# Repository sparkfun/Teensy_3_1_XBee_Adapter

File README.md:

SparkFun Teensy 3.1 XBee Adapter
=================================

[*SparkFun Teensy 3.1 XBee Adapter (BOB-13311)*](https://www.sparkfun.com/products/13311)

Adapter board from the Teensy3.1 to XBee radio modules.

Repository Contents
-------------------

* **/Documentation** - Datasheets, tutorial images. 
* **/Firmware** - Example code 
* **/Hardware** - Eagle design files (.brd, .sch)
* **/Production** - Production panel files (.brd)

Documentation
--------------
* **[Hookup Guide](https://learn.sparkfun.com/tutorials/teensy-xbee-adapter-hookup-guide)** - Basic hookup guide for the Teensy XBee Adapter.

License Information
-------------------
This product is _**open source**_! 

The **hardware** is released under [Creative Commons ShareAlike 4.0 International](https://creativecommons.org/licenses/by-sa/4.0/).
The firmware is released under the [MIT License](http://opensource.org/licenses/MIT). 

Please use, reuse, and modify these files as you see fit. Please maintain attribution to SparkFun Electronics and release anything derivative under the same license.

Distributed as-is; no warranty is given.

- Your friends at SparkFun.

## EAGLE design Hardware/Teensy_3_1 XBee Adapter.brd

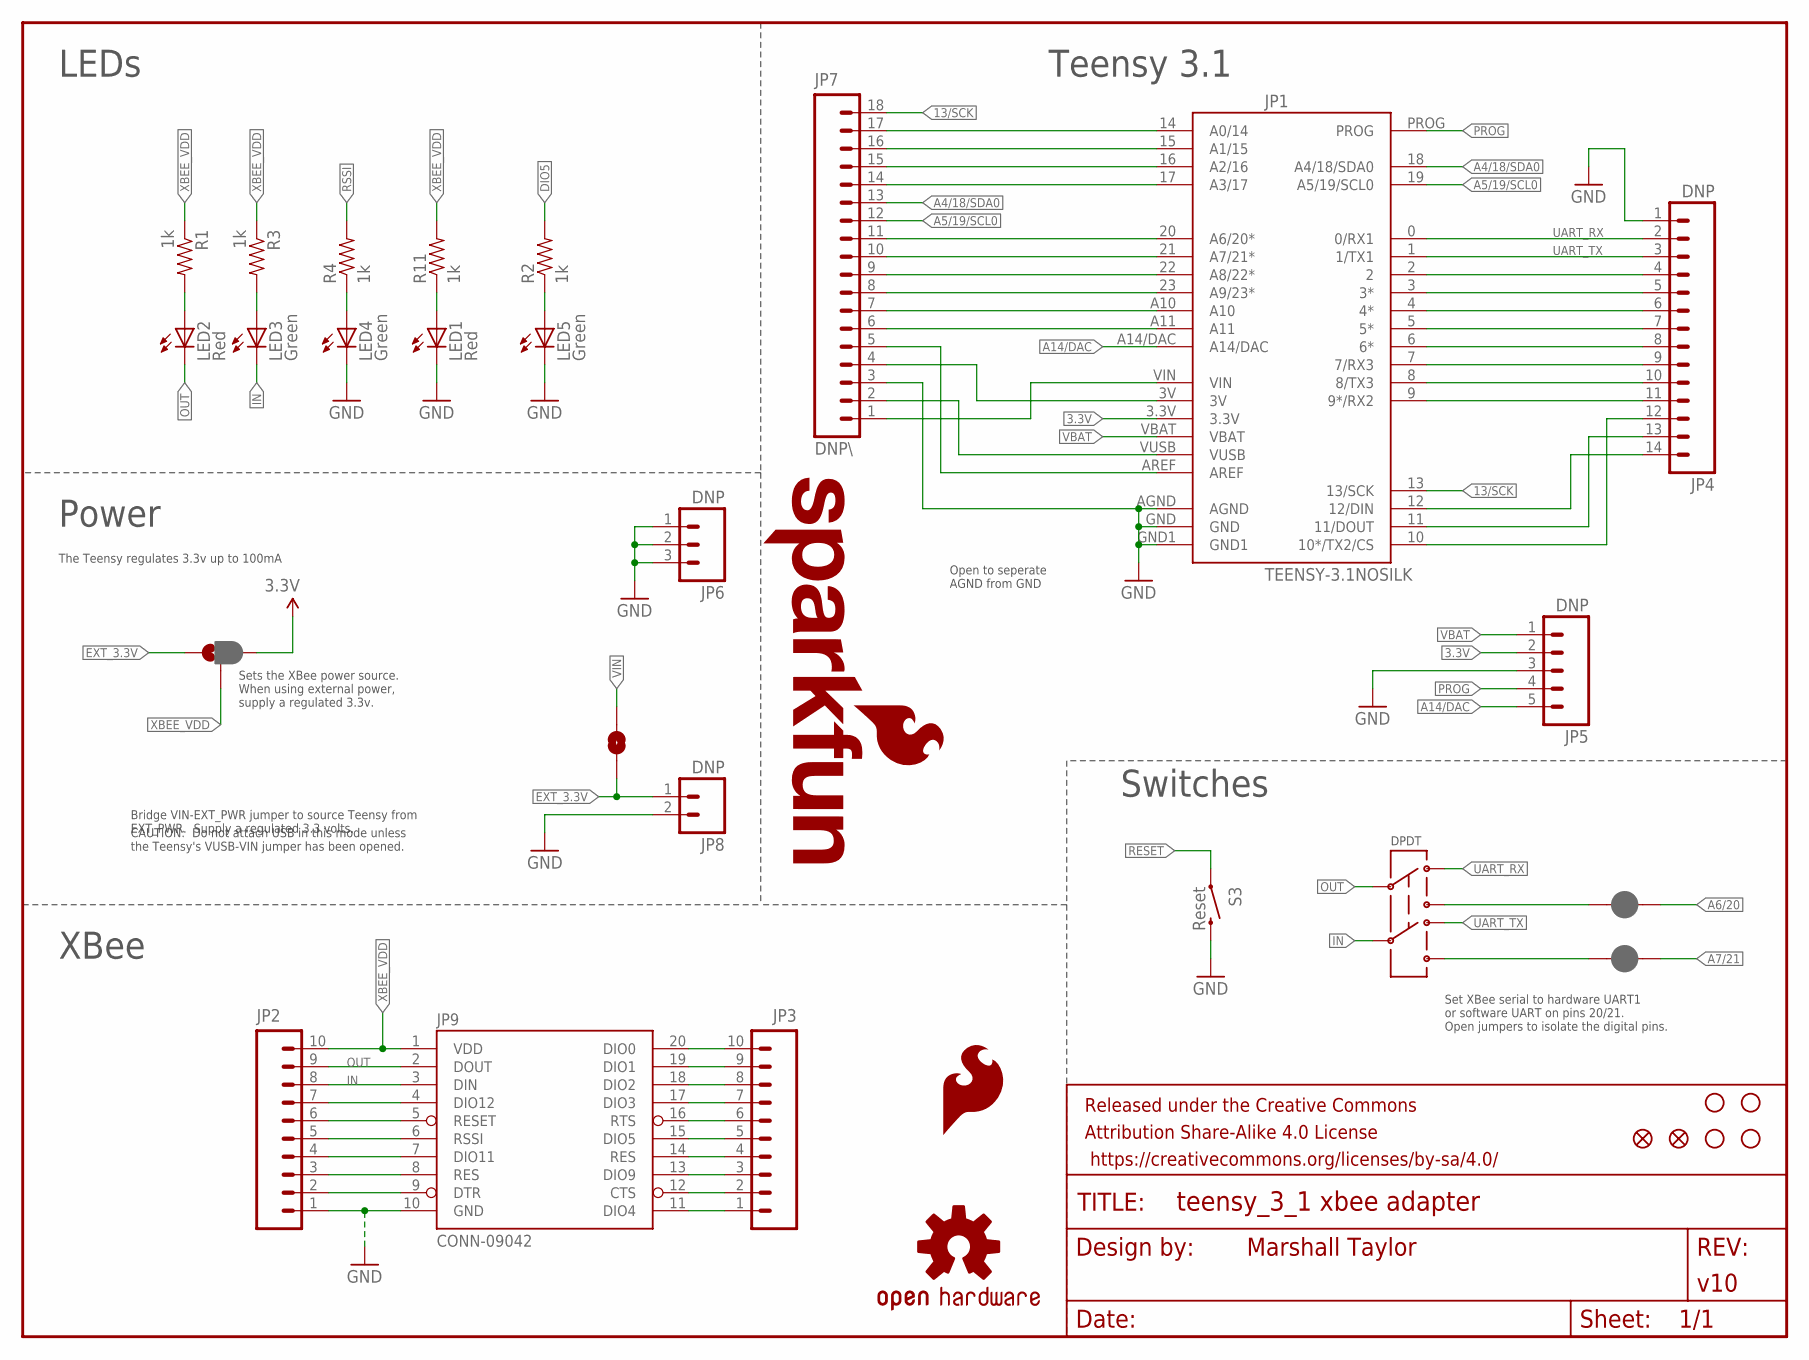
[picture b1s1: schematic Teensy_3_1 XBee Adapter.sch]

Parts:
FID1, FID2: FIDUCIAL1X2; FIDUCIAL-1X2
FRAME1: FRAME-LETTER; CREATIVE_COMMONS
JP1: TEENSY-3.1NOSILK; TEENSY-3.1_NOSILK
JP2, JP3: M10NO_SILK_PTH_FEMALE; 1X10_NO_SILK
JP4: DNP; 1X14
JP5: DNP; 1X05
JP6: DNP; 1X03
JP7: DNP\; 1X18
JP8: DNP; 1X02
JP9: CONN-09042; XBEE-SMD
LED1, LED2: Red; LED-0603
LED3, LED4, LED5: Green; LED-0603
LOGO1: SFE_LOGO_FLAME.2_INCH; SFE_LOGO_FLAME_.2
LOGO2: OSHW-LOGOM; OSHW-LOGO-M
LOGO3: SFE_LOGO_NAME_FLAME.2_INCH; SFE_LOGO_NAME_FLAME_.2
R1, R2, R3, R4, R11: 1k; 0603-RES
S2: DPDT; AYZ0202
S3: Reset; TACTILE-SWITCH-SMD
SJ1: D_TX; PAD-JUMPER-2-NC_BY_PASTE_YES_SILK
SJ3: D_RX; PAD-JUMPER-2-NC_BY_PASTE_YES_SILK
SJ4: JUMPER-PAD-3-2OF3_NC_BY_PASTE; PAD-JUMPER-3-2OF3_NC_BY_PASTE_YES_SILK_FULL_BOX
SJ5: EXT_JPR; PAD-JUMPER-2-NO_YES_SILK
STANDOFF1, STANDOFF2, STANDOFF3, STANDOFF4: STAND-OFF

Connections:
2: JP1.2, JP4.4
3: JP1.3 (3*), JP4.5
3.3V: JP1.3.3V, JP5.2, SJ4.3
3V: JP1.3V, JP7.4
4: JP1.4 (4*), JP4.6
5: JP1.5 (5*), JP4.7
6: JP1.6 (6*), JP4.8
7/RX3: JP1.7 (7/RX3), JP4.9
8/TX3: JP1.8 (8/TX3), JP4.10
9/RX2: JP1.9 (9*/RX2), JP4.11
10/TX2/CS: JP1.10 (10*/TX2/CS), JP4.12
11/DOUT: JP1.11 (11/DOUT), JP4.13
12/DIN: JP1.12 (12/DIN), JP4.14
13/SCK: JP1.13 (13/SCK), JP7.18
A0/14: JP1.14 (A0/14), JP7.17
A1/15: JP1.15 (A1/15), JP7.16
A2/16: JP1.16 (A2/16), JP7.15
A3/17: JP1.17 (A3/17), JP7.14
A4/18/SDA0: JP1.18 (A4/18/SDA0), JP7.13
A5/19/SCL0: JP1.19 (A5/19/SCL0), JP7.12
A6/20: JP1.20 (A6/20*), JP7.11, SJ3.1
A7/21: JP1.21 (A7/21*), JP7.10, SJ1.1
A8/22: JP1.22 (A8/22*), JP7.9
A9/23: JP1.23 (A9/23*), JP7.8
A10: JP1.A10, JP7.7
A11: JP1.A11, JP7.6
A14/DAC: JP1.A14/DAC, JP5.5
AREF: JP1.AREF, JP7.5
CTS: JP3.2, JP9.12 (CTS)
DIO0: JP3.10, JP9.20 (DIO0)
DIO1: JP3.9, JP9.19 (DIO1)
DIO2: JP3.8, JP9.18 (DIO2)
DIO3: JP3.7, JP9.17 (DIO3)
DIO4: JP3.1, JP9.11 (DIO4)
DIO5: JP3.5, JP9.15 (DIO5), R2.2
DIO9: JP3.3, JP9.13 (DIO9)
DIO11: JP2.4, JP9.7 (DIO11)
DIO12: JP2.7, JP9.4 (DIO12)
DTR: JP2.2, JP9.9 (DTR)
EXT_3.3V: JP8.1, SJ4.1, SJ5.2
GND: JP1.AGND, JP1.GND, JP1.GND1, JP2.1, JP4.1, JP5.3, JP6.1, JP6.2, JP6.3, JP7.3, JP8.2, JP9.10 (GND), LED1.C, LED4.C, LED5.C, S3.3 (2)
IN: JP2.8, JP9.3 (DIN), LED3.C, S2.5
unnamed: LED1.A, R11.1
unnamed: LED2.A, R1.2
unnamed: LED3.A, R3.2
unnamed: LED4.A, R4.1
unnamed: LED5.A, R2.1
unnamed: S2.6, SJ1.2
unnamed: S2.3, SJ3.2
OUT: JP2.9, JP9.2 (DOUT), LED2.C, S2.2
PROG: JP1.PROG, JP5.4
RES: JP2.3, JP9.8 (RES)
RES2: JP3.4, JP9.14 (RES)
RESET: JP2.6, JP9.5 (RESET), S3.1
RSSI: JP2.5, JP9.6 (RSSI), R4.2
RTS: JP3.6, JP9.16 (RTS)
UART_RX: JP1.0 (0/RX1), JP4.2, S2.1
UART_TX: JP1.1 (1/TX1), JP4.3, S2.4
VBAT: JP1.VBAT, JP5.1
VIN: JP1.VIN, JP7.1, SJ5.1
VUSB: JP1.VUSB, JP7.2
XBEE_VDD: JP2.10, JP9.1 (VDD), R1.1, R3.1, R11.2, SJ4.2

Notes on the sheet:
Switches
Teensy 3.1
XBee
Power
LEDs
The Teensy regulates 3.3v up to 100mA
Sets the XBee power source. When using external power, supply a regulated 3.3v.
Bridge VIN-EXT_PWR jumper to source Teensy from EXT_PWR. Supply a regulated 3.3 volts.
CAUTION: Do not attach USB in this mode unless the Teensy's VUSB-VIN jumper has been opened.
Set XBee serial to hardware UART1 or software UART on pins 20/21. Open jumpers to isolate the digital pins.
DPDT
Open to seperate AGND from GND

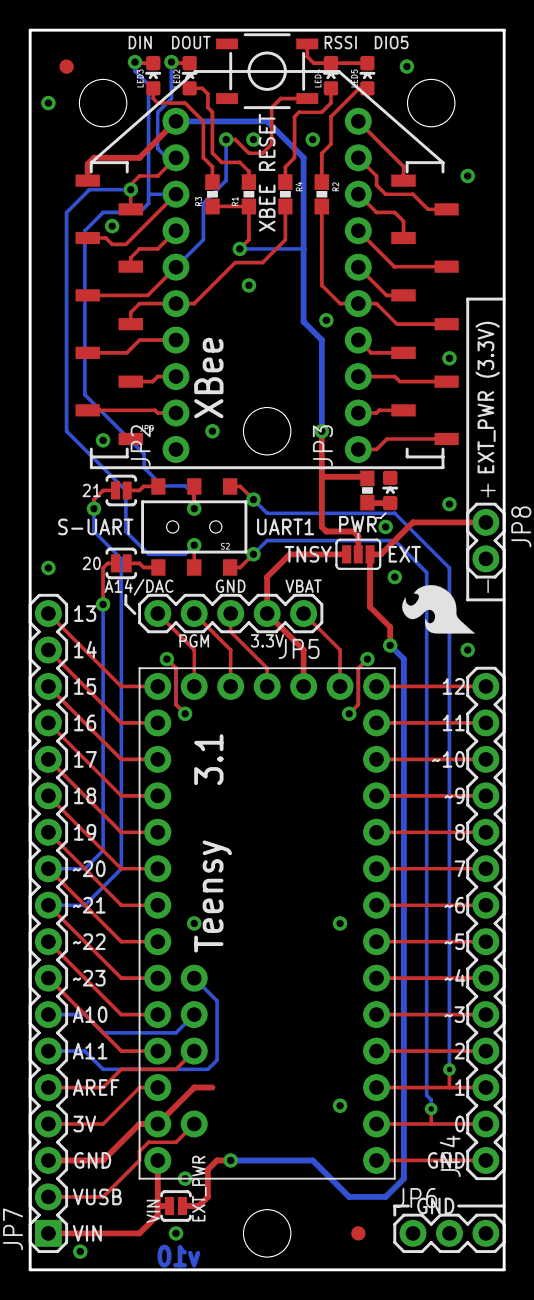
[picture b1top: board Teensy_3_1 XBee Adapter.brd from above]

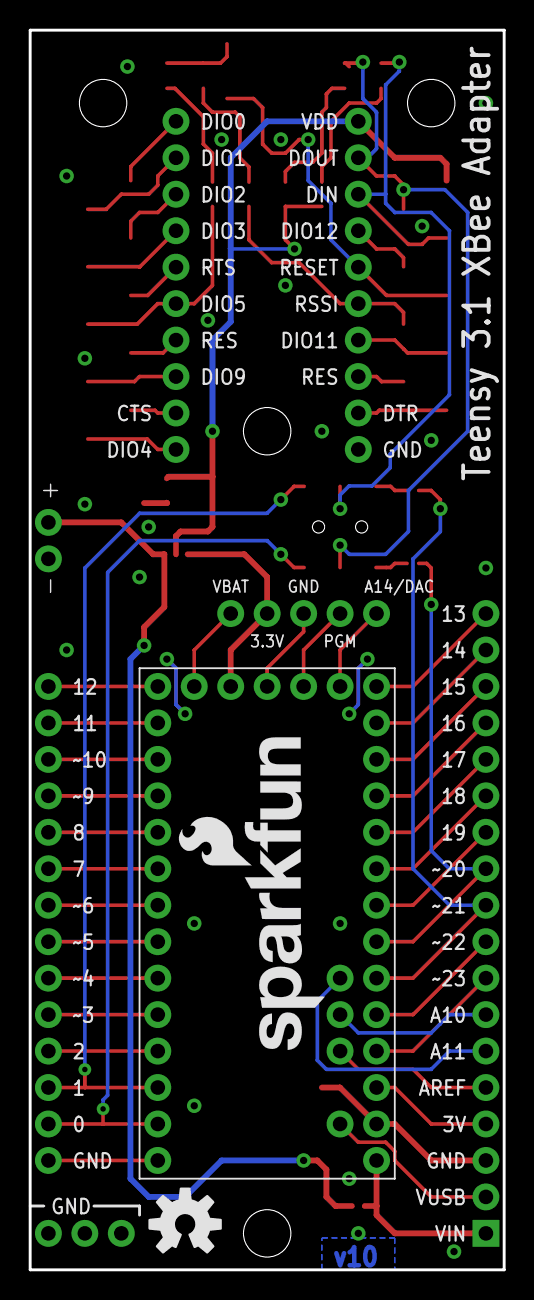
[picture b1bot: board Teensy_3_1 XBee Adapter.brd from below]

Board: 2 copper layers, 33.0 x 86.4 mm, 35 parts (2 on the bottom side), 62 nets.

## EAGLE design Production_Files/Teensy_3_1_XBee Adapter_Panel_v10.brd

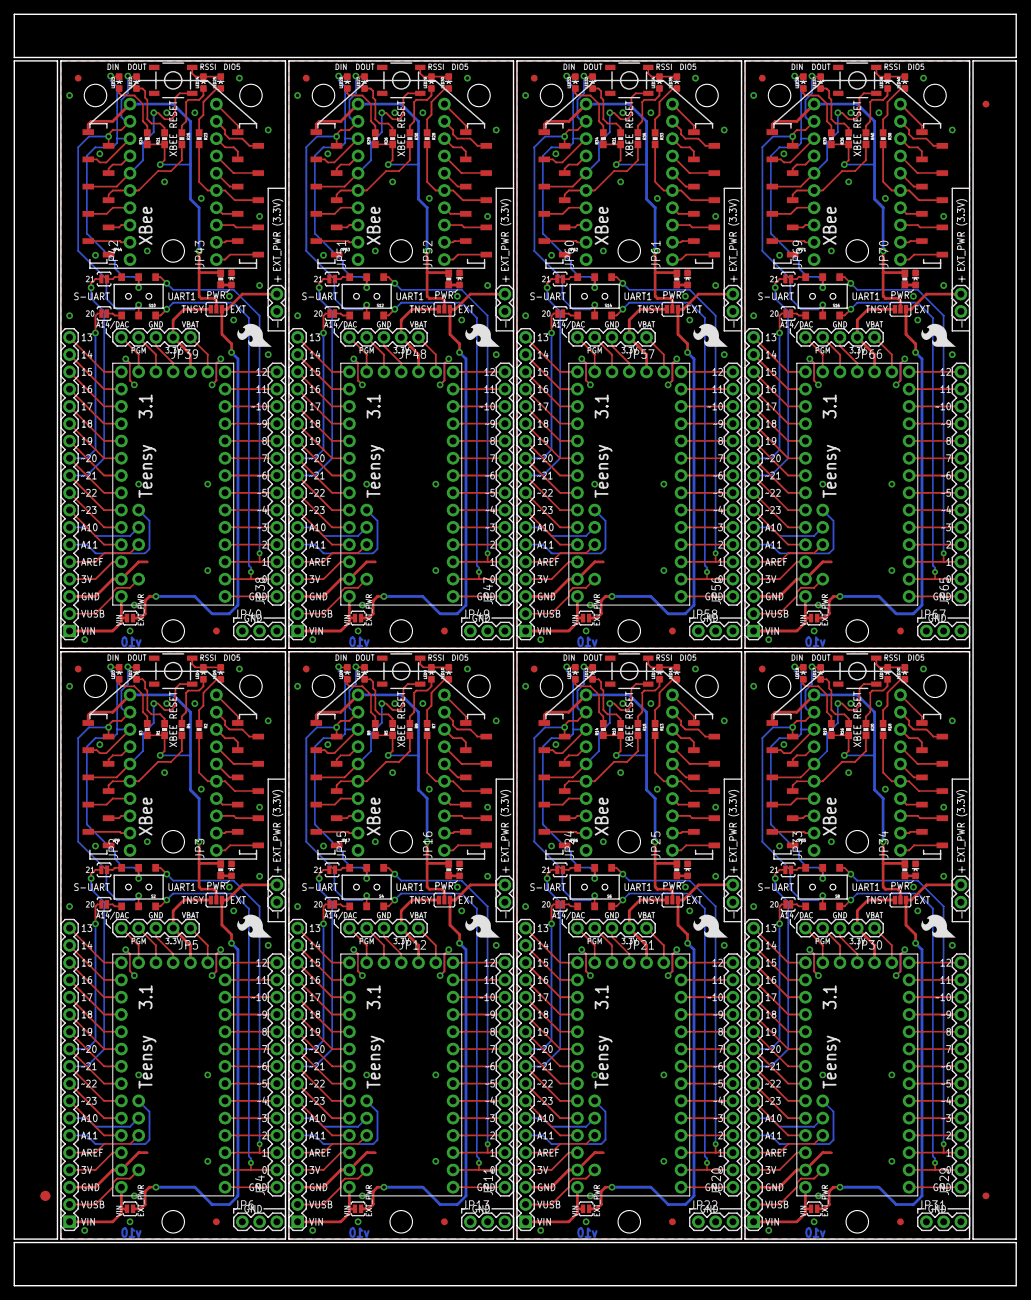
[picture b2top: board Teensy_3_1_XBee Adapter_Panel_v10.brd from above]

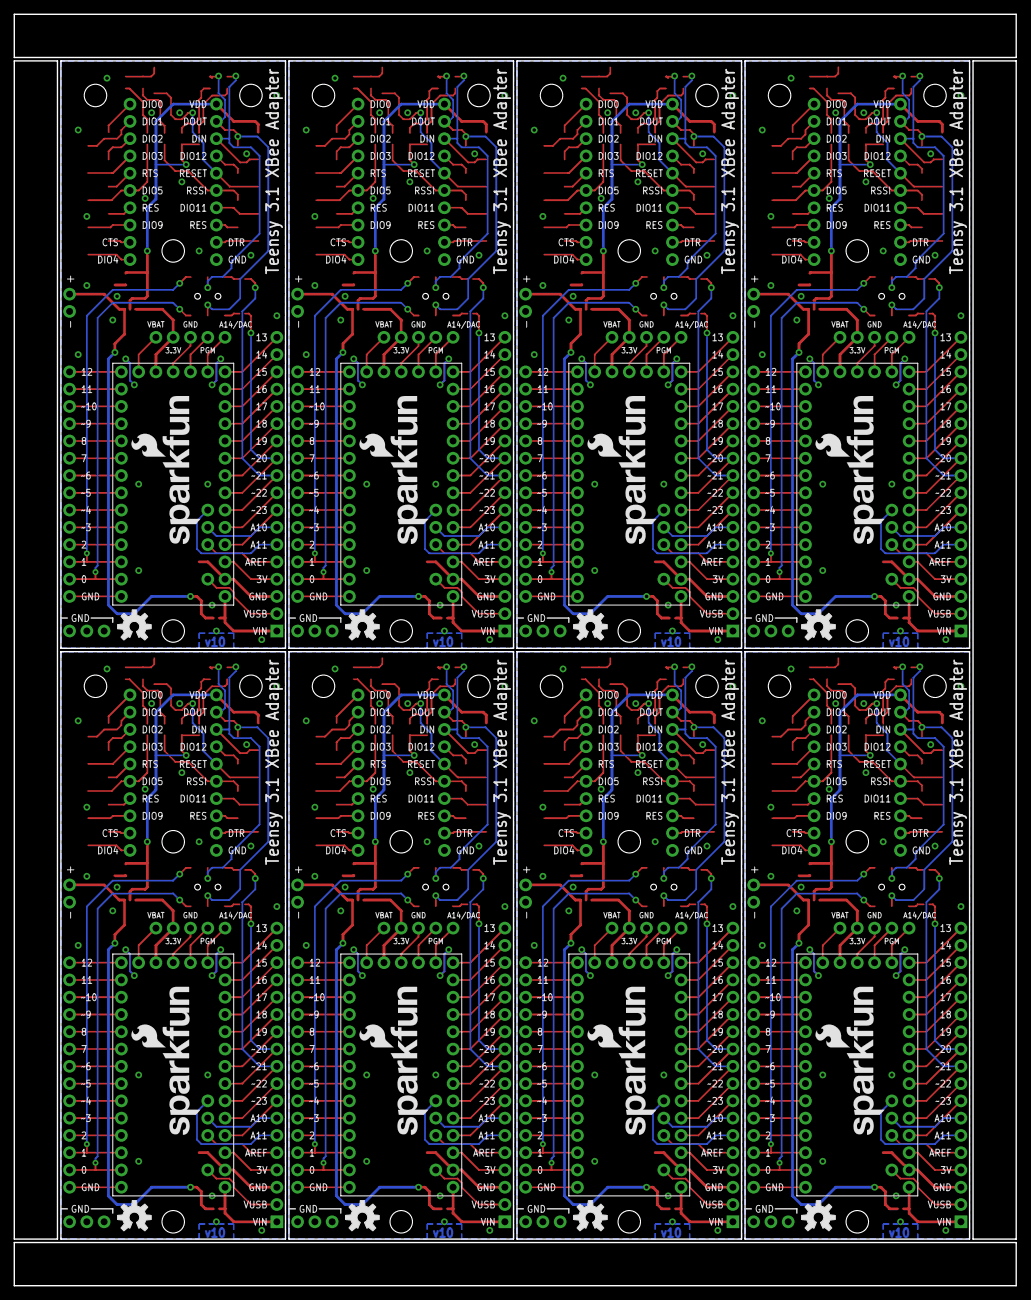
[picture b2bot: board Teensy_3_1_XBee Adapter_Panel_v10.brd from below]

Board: 2 copper layers, 147.3 x 186.9 mm, 275 parts (16 on the bottom side), 496 nets.

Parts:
E$1: FIDUCIAL-1.5X3
E$4, E$5: FIDUCIAL-1X2
FID1, FID2, FID3, FID4, FID5, FID6, FID7, FID8, FID9, FID10, FID11, FID12, FID13, FID14, FID15, FID16: FIDUCIAL1X2; FIDUCIAL-1X2
JP1, JP10, JP19, JP28, JP37, JP46, JP55, JP64: TEENSY-3.1NOSILK; TEENSY-3.1_NOSILK
JP2, JP3, JP15, JP16, JP24, JP25, JP33, JP34, JP42, JP43, JP51, JP52, JP60, JP61, JP69, JP70: 1X10_NO_SILK
JP4, JP11, JP20, JP29, JP38, JP47, JP56, JP65: DNP; 1X14
JP5, JP12, JP21, JP30, JP39, JP48, JP57, JP66: DNP; 1X05
JP6, JP13, JP22, JP31, JP40, JP49, JP58, JP67: DNP; 1X03
JP7, JP14, JP23, JP32, JP41, JP50, JP59, JP68: DNP\; 1X18
JP8, JP18, JP27, JP36, JP45, JP54, JP63, JP72: DNP; 1X02
JP9, JP17, JP26, JP35, JP44, JP53, JP62, JP71: CONN-09042; XBEE-SMD
LED1, LED2, LED6, LED7, LED11, LED12, LED16, LED17, LED21, LED22, LED26, LED27, LED31, LED32, LED36, LED37: Red; LED-0603
LED3, LED4, LED5, LED8, LED9, LED10, LED13, LED14, LED15, LED18, LED19, LED20, LED23, LED24, LED25, LED28, LED29, LED30, LED33, LED34, LED35, LED38, LED39, LED40: Green; LED-0603
LOGO1, LOGO6, LOGO9, LOGO12, LOGO15, LOGO18, LOGO21, LOGO24: SFE_LOGO_FLAME.2_INCH; SFE_LOGO_FLAME_.2
LOGO2, LOGO4, LOGO7, LOGO10, LOGO13, LOGO16, LOGO19, LOGO22: OSHW-LOGOM; OSHW-LOGO-M
LOGO3, LOGO5, LOGO8, LOGO11, LOGO14, LOGO17, LOGO20, LOGO23: SFE_LOGO_NAME_FLAME.2_INCH; SFE_LOGO_NAME_FLAME_.2
R1, R2, R3, R4, R5, R6, R7, R8, R9, R10, R11, R12, R13, R14, R15, R16, R17, R18, R19, R20, R21, R22, R23, R24, R25, R26, R27, R28, R29, R30, R31, R32, R33, R34, R35, R36, R37, R38, R39, R40: 1k; 0603-RES
S1, S3, S5, S7, S9, S11, S13, S15: Reset; TACTILE-SWITCH-SMD
S2, S4, S6, S8, S10, S12, S14, S16: DPDT; AYZ0202
SJ1, SJ2, SJ9, SJ13, SJ17, SJ21, SJ25, SJ29: D_TX; PAD-JUMPER-2-NC_BY_PASTE_YES_SILK
SJ3, SJ6, SJ10, SJ14, SJ18, SJ22, SJ26, SJ30: D_RX; PAD-JUMPER-2-NC_BY_PASTE_YES_SILK
SJ4, SJ7, SJ11, SJ15, SJ19, SJ23, SJ27, SJ31: JUMPER-PAD-3-2OF3_NC_BY_PASTE; PAD-JUMPER-3-2OF3_NC_BY_PASTE_YES_SILK_FULL_BOX
SJ5, SJ8, SJ12, SJ16, SJ20, SJ24, SJ28, SJ32: EXT_JPR; PAD-JUMPER-2-NO_YES_SILK
STANDOFF1, STANDOFF2, STANDOFF3, STANDOFF4, STANDOFF5, STANDOFF6, STANDOFF7, STANDOFF8, STANDOFF9, STANDOFF10, STANDOFF11, STANDOFF12, STANDOFF13, STANDOFF14, STANDOFF15, STANDOFF16, STANDOFF17, STANDOFF18, STANDOFF19, STANDOFF20, STANDOFF21, STANDOFF22, STANDOFF23, STANDOFF24, STANDOFF25, STANDOFF26, STANDOFF27, STANDOFF28, STANDOFF29, STANDOFF30, STANDOFF31, STANDOFF32: STAND-OFF

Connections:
1: JP10.2, JP11.4
2: JP1.2, JP4.4
3: JP1.3, JP4.5
3.3V: JP1.3.3V, JP5.2, SJ4.3
3.3V1: JP10.3.3V, JP12.2, SJ7.3
3.3V2: JP19.3.3V, JP21.2, SJ11.3
3.3V3: JP28.3.3V, JP30.2, SJ15.3
3.3V4: JP37.3.3V, JP39.2, SJ19.3
3.3V5: JP46.3.3V, JP48.2, SJ23.3
3.3V6: JP55.3.3V, JP57.2, SJ27.3
3.3V7: JP64.3.3V, JP66.2, SJ31.3
3V: JP1.3V, JP7.4
3V1: JP10.3V, JP14.4
3V2: JP19.3V, JP23.4
3V3: JP28.3V, JP32.4
3V4: JP37.3V, JP41.4
3V5: JP46.3V, JP50.4
3V6: JP55.3V, JP59.4
3V7: JP64.3V, JP68.4
4: JP1.4, JP4.6
5: JP1.5, JP4.7
6: JP1.6, JP4.8
7: JP10.4, JP11.6
7/RX1: JP10.7, JP11.9
7/RX2: JP19.7, JP20.9
7/RX3: JP1.7, JP4.9
7/RX4: JP28.7, JP29.9
7/RX5: JP37.7, JP38.9
7/RX6: JP46.7, JP47.9
7/RX7: JP55.7, JP56.9
7/RX8: JP64.7, JP65.9
8: JP10.5, JP11.7
8/TX1: JP10.8, JP11.10
8/TX2: JP19.8, JP20.10
8/TX3: JP1.8, JP4.10
8/TX4: JP28.8, JP29.10
8/TX5: JP37.8, JP38.10
8/TX6: JP46.8, JP47.10
8/TX7: JP55.8, JP56.10
8/TX8: JP64.8, JP65.10
9: JP10.6, JP11.8
9/RX1: JP10.9, JP11.11
9/RX2: JP1.9, JP4.11
9/RX3: JP19.9, JP20.11
9/RX4: JP28.9, JP29.11
9/RX5: JP37.9, JP38.11
9/RX6: JP46.9, JP47.11
9/RX7: JP55.9, JP56.11
9/RX8: JP64.9, JP65.11
10: JP10.3, JP11.5
10/TX2/CS: JP1.10, JP4.12
10/TX2/CS1: JP10.10, JP11.12
10/TX2/CS2: JP19.10, JP20.12
10/TX2/CS3: JP28.10, JP29.12
10/TX2/CS4: JP37.10, JP38.12
10/TX2/CS5: JP46.10, JP47.12
10/TX2/CS6: JP55.10, JP56.12
10/TX2/CS7: JP64.10, JP65.12
11: JP19.2, JP20.4
11/DOUT: JP1.11, JP4.13
11/DOUT1: JP10.11, JP11.13
11/DOUT2: JP19.11, JP20.13
11/DOUT3: JP28.11, JP29.13
11/DOUT4: JP37.11, JP38.13
11/DOUT5: JP46.11, JP47.13
11/DOUT6: JP55.11, JP56.13
11/DOUT7: JP64.11, JP65.13
12: JP19.4, JP20.6
12/DIN: JP1.12, JP4.14
12/DIN1: JP10.12, JP11.14
12/DIN2: JP19.12, JP20.14
12/DIN3: JP28.12, JP29.14
12/DIN4: JP37.12, JP38.14
12/DIN5: JP46.12, JP47.14
12/DIN6: JP55.12, JP56.14
12/DIN7: JP64.12, JP65.14
13: JP19.5, JP20.7
13/SCK: JP1.13, JP7.18
13/SCK1: JP10.13, JP14.18
13/SCK2: JP19.13, JP23.18
13/SCK3: JP28.13, JP32.18
13/SCK4: JP37.13, JP41.18
13/SCK5: JP46.13, JP50.18
13/SCK6: JP55.13, JP59.18
13/SCK7: JP64.13, JP68.18
14: JP19.6, JP20.8
15: JP19.3, JP20.5
16: JP28.2, JP29.4
17: JP28.4, JP29.6
18: JP28.5, JP29.7
19: JP28.6, JP29.8
20: JP28.3, JP29.5
21: JP37.2, JP38.4
22: JP37.4, JP38.6
23: JP37.5, JP38.7
24: JP37.6, JP38.8
25: JP37.3, JP38.5
26: JP46.2, JP47.4
27: JP46.4, JP47.6
28: JP46.5, JP47.7
29: JP46.6, JP47.8
30: JP46.3, JP47.5
31: JP55.2, JP56.4
32: JP55.4, JP56.6
33: JP55.5, JP56.7
34: JP55.6, JP56.8
35: JP55.3, JP56.5
36: JP64.2, JP65.4
37: JP64.4, JP65.6
38: JP64.5, JP65.7
39: JP64.6, JP65.8
40: JP64.3, JP65.5
A0/1: JP10.14, JP14.17
A0/2: JP19.14, JP23.17
A0/3: JP28.14, JP32.17
A0/4: JP37.14, JP41.17
A0/5: JP46.14, JP50.17
A0/6: JP55.14, JP59.17
A0/7: JP64.14, JP68.17
A0/14: JP1.14, JP7.17
A1: JP10.A10, JP14.7
A1/1: JP10.15, JP14.16
A1/2: JP19.15, JP23.16
A1/3: JP28.15, JP32.16
A1/4: JP37.15, JP41.16
A1/5: JP46.15, JP50.16
A1/6: JP55.15, JP59.16
A1/7: JP64.15, JP68.16
A1/15: JP1.15, JP7.16
A2: JP10.A11, JP14.6
A2/1: JP10.16, JP14.15
A2/2: JP19.16, JP23.15
A2/3: JP28.16, JP32.15
A2/4: JP37.16, JP41.15
A2/5: JP46.16, JP50.15
A2/6: JP55.16, JP59.15
A2/7: JP64.16, JP68.15
A2/16: JP1.16, JP7.15
A3: JP19.A10, JP23.7
A3/1: JP10.17, JP14.14
A3/2: JP19.17, JP23.14
A3/3: JP28.17, JP32.14
A3/4: JP37.17, JP41.14
A3/5: JP46.17, JP50.14
A3/6: JP55.17, JP59.14
A3/7: JP64.17, JP68.14
A3/17: JP1.17, JP7.14
A4: JP19.A11, JP23.6
A4/18/SDA0: JP1.18, JP7.13
A4/18/SDA1: JP10.18, JP14.13
A4/18/SDA2: JP19.18, JP23.13
A4/18/SDA3: JP28.18, JP32.13
A4/18/SDA4: JP37.18, JP41.13
A4/18/SDA5: JP46.18, JP50.13
A4/18/SDA6: JP55.18, JP59.13
A4/18/SDA7: JP64.18, JP68.13
A5: JP28.A10, JP32.7
A5/19/SCL0: JP1.19, JP7.12
A5/19/SCL1: JP10.19, JP14.12
A5/19/SCL2: JP19.19, JP23.12
A5/19/SCL3: JP28.19, JP32.12
A5/19/SCL4: JP37.19, JP41.12
A5/19/SCL5: JP46.19, JP50.12
A5/19/SCL6: JP55.19, JP59.12
A5/19/SCL7: JP64.19, JP68.12
A6: JP28.A11, JP32.6
A6/1: JP10.20, JP14.11, SJ6.1
A6/2: JP19.20, JP23.11, SJ10.1
A6/3: JP28.20, JP32.11, SJ14.1
A6/4: JP37.20, JP41.11, SJ18.1
A6/5: JP46.20, JP50.11, SJ22.1
A6/6: JP55.20, JP59.11, SJ26.1
A6/7: JP64.20, JP68.11, SJ30.1
A6/20: JP1.20, JP7.11, SJ3.1
A7: JP37.A10, JP41.7
A7/1: JP10.21, JP14.10, SJ2.1
A7/2: JP19.21, JP23.10, SJ9.1
A7/3: JP28.21, JP32.10, SJ13.1
A7/4: JP37.21, JP41.10, SJ17.1
A7/5: JP46.21, JP50.10, SJ21.1
A7/6: JP55.21, JP59.10, SJ25.1
A7/7: JP64.21, JP68.10, SJ29.1
A7/21: JP1.21, JP7.10, SJ1.1
A8: JP37.A11, JP41.6
A8/1: JP10.22, JP14.9
A8/2: JP19.22, JP23.9
A8/3: JP28.22, JP32.9
A8/4: JP37.22, JP41.9
A8/5: JP46.22, JP50.9
A8/6: JP55.22, JP59.9
A8/7: JP64.22, JP68.9
A8/22: JP1.22, JP7.9
A9: JP46.A10, JP50.7
A9/1: JP10.23, JP14.8
A9/2: JP19.23, JP23.8
A9/3: JP28.23, JP32.8
A9/4: JP37.23, JP41.8
A9/5: JP46.23, JP50.8
A9/6: JP55.23, JP59.8
A9/7: JP64.23, JP68.8
A9/23: JP1.23, JP7.8
A10: JP1.A10, JP7.7
A11: JP1.A11, JP7.6
A12: JP46.A11, JP50.6
A13: JP55.A10, JP59.7
A14: JP55.A11, JP59.6
A14/DAC: JP1.A14/DAC, JP5.5
A14/DAC1: JP10.A14/DAC, JP12.5
A14/DAC2: JP19.A14/DAC, JP21.5
A14/DAC3: JP28.A14/DAC, JP30.5
A14/DAC4: JP37.A14/DAC, JP39.5
A14/DAC5: JP46.A14/DAC, JP48.5
A14/DAC6: JP55.A14/DAC, JP57.5
A14/DAC7: JP64.A14/DAC, JP66.5
A15: JP64.A10, JP68.7
A16: JP64.A11, JP68.6
AREF: JP1.AREF, JP7.5
AREF1: JP10.AREF, JP14.5
AREF2: JP19.AREF, JP23.5
AREF3: JP28.AREF, JP32.5
AREF4: JP37.AREF, JP41.5
AREF5: JP46.AREF, JP50.5
AREF6: JP55.AREF, JP59.5
AREF7: JP64.AREF, JP68.5
CTS: JP3.2, JP9.12
CTS1: JP16.2, JP17.12
CTS2: JP25.2, JP26.12
CTS3: JP34.2, JP35.12
CTS4: JP43.2, JP44.12
CTS5: JP52.2, JP53.12
CTS6: JP61.2, JP62.12
CTS7: JP70.2, JP71.12
DIO0: JP3.10, JP9.20
DIO1: JP3.9, JP9.19
DIO2: JP3.8, JP9.18
DIO3: JP3.7, JP9.17
DIO4: JP3.1, JP9.11
DIO5: JP3.5, JP9.15, R2.2
DIO6: JP16.1, JP17.11
DIO7: JP16.3, JP17.13
DIO8: JP16.7, JP17.17
DIO9: JP3.3, JP9.13
DIO10: JP16.8, JP17.18
DIO11: JP2.4, JP9.7
DIO12: JP2.7, JP9.4
DIO13: JP16.9, JP17.19
DIO14: JP16.10, JP17.20
DIO15: JP15.4, JP17.7
DIO16: JP15.7, JP17.4
DIO17: JP16.5, JP17.15, R7.2
DIO18: JP25.1, JP26.11
DIO19: JP25.3, JP26.13
DIO20: JP25.7, JP26.17
DIO21: JP25.8, JP26.18
DIO22: JP25.9, JP26.19
DIO23: JP25.10, JP26.20
DIO24: JP24.4, JP26.7
DIO25: JP24.7, JP26.4
DIO26: JP25.5, JP26.15, R13.2
DIO27: JP34.1, JP35.11
DIO28: JP34.3, JP35.13
DIO29: JP34.7, JP35.17
DIO30: JP34.8, JP35.18
DIO31: JP34.9, JP35.19
DIO32: JP34.10, JP35.20
DIO33: JP33.4, JP35.7
DIO34: JP33.7, JP35.4
DIO35: JP34.5, JP35.15, R18.2
DIO36: JP43.1, JP44.11
DIO37: JP43.3, JP44.13
DIO38: JP43.7, JP44.17
DIO39: JP43.8, JP44.18
DIO40: JP43.9, JP44.19
DIO41: JP43.10, JP44.20
DIO42: JP42.4, JP44.7
DIO43: JP42.7, JP44.4
DIO44: JP43.5, JP44.15, R23.2
DIO45: JP52.1, JP53.11
DIO46: JP52.3, JP53.13
DIO47: JP52.7, JP53.17
DIO48: JP52.8, JP53.18
DIO49: JP52.9, JP53.19
DIO50: JP52.10, JP53.20
DIO51: JP51.4, JP53.7
DIO52: JP51.7, JP53.4
DIO53: JP52.5, JP53.15, R28.2
DIO54: JP61.1, JP62.11
DIO55: JP61.3, JP62.13
DIO56: JP61.7, JP62.17
DIO57: JP61.8, JP62.18
DIO58: JP61.9, JP62.19
DIO59: JP61.10, JP62.20
DIO60: JP60.4, JP62.7
DIO61: JP60.7, JP62.4
DIO62: JP61.5, JP62.15, R33.2
DIO63: JP70.1, JP71.11
DIO64: JP70.3, JP71.13
DIO65: JP70.7, JP71.17
DIO66: JP70.8, JP71.18
DIO67: JP70.9, JP71.19
DIO68: JP70.10, JP71.20
DIO69: JP69.4, JP71.7
DIO70: JP69.7, JP71.4
DIO71: JP70.5, JP71.15, R38.2
DTR: JP2.2, JP9.9
DTR1: JP15.2, JP17.9
DTR2: JP24.2, JP26.9
DTR3: JP33.2, JP35.9
DTR4: JP42.2, JP44.9
DTR5: JP51.2, JP53.9
DTR6: JP60.2, JP62.9
DTR7: JP69.2, JP71.9
EXT_3.3V: JP8.1, SJ4.1, SJ5.2
EXT_3.3V1: JP18.1, SJ7.1, SJ8.2
EXT_3.3V2: JP27.1, SJ11.1, SJ12.2
EXT_3.3V3: JP36.1, SJ15.1, SJ16.2
EXT_3.3V4: JP45.1, SJ19.1, SJ20.2
EXT_3.3V5: JP54.1, SJ23.1, SJ24.2
EXT_3.3V6: JP63.1, SJ27.1, SJ28.2
EXT_3.3V7: JP72.1, SJ31.1, SJ32.2
GND: JP1.AGND, JP1.GND, JP1.GND1, JP2.1, JP4.1, JP5.3, JP6.1, JP6.2, JP6.3, JP7.3, JP8.2, JP9.10, LED1.C, LED4.C, LED5.C, S3.3
GND1: JP10.AGND, JP10.GND, JP10.GND1, JP11.1, JP12.3, JP13.1, JP13.2, JP13.3, JP14.3, JP15.1, JP17.10, JP18.2, LED6.C, LED9.C, LED10.C, S1.3
GND2: JP19.AGND, JP19.GND, JP19.GND1, JP20.1, JP21.3, JP22.1, JP22.2, JP22.3, JP23.3, JP24.1, JP26.10, JP27.2, LED11.C, LED14.C, LED15.C, S5.3
GND3: JP28.AGND, JP28.GND, JP28.GND1, JP29.1, JP30.3, JP31.1, JP31.2, JP31.3, JP32.3, JP33.1, JP35.10, JP36.2, LED16.C, LED19.C, LED20.C, S7.3
GND4: JP37.AGND, JP37.GND, JP37.GND1, JP38.1, JP39.3, JP40.1, JP40.2, JP40.3, JP41.3, JP42.1, JP44.10, JP45.2, LED21.C, LED24.C, LED25.C, S9.3
GND5: JP46.AGND, JP46.GND, JP46.GND1, JP47.1, JP48.3, JP49.1, JP49.2, JP49.3, JP50.3, JP51.1, JP53.10, JP54.2, LED26.C, LED29.C, LED30.C, S11.3
GND6: JP55.AGND, JP55.GND, JP55.GND1, JP56.1, JP57.3, JP58.1, JP58.2, JP58.3, JP59.3, JP60.1, JP62.10, JP63.2, LED31.C, LED34.C, LED35.C, S13.3
GND7: JP64.AGND, JP64.GND, JP64.GND1, JP65.1, JP66.3, JP67.1, JP67.2, JP67.3, JP68.3, JP69.1, JP71.10, JP72.2, LED36.C, LED39.C, LED40.C, S15.3
IN: JP2.8, JP9.3, LED3.C, S2.5
IN1: JP15.8, JP17.3, LED8.C, S4.5
IN2: JP24.8, JP26.3, LED13.C, S6.5
IN3: JP33.8, JP35.3, LED18.C, S8.5
IN4: JP42.8, JP44.3, LED23.C, S10.5
IN5: JP51.8, JP53.3, LED28.C, S12.5
IN6: JP60.8, JP62.3, LED33.C, S14.5
IN7: JP69.8, JP71.3, LED38.C, S16.5
unnamed: S4.6, SJ2.2
unnamed: S4.3, SJ6.2
unnamed: LED6.A, R6.1
unnamed: LED7.A, R5.2
unnamed: LED8.A, R8.2
unnamed: LED9.A, R9.1
unnamed: LED10.A, R7.1
unnamed: S6.6, SJ9.2
unnamed: S6.3, SJ10.2
unnamed: LED11.A, R12.1
unnamed: LED12.A, R10.2
unnamed: LED1.A, R11.1
unnamed: LED13.A, R14.2
unnamed: LED14.A, R15.1
unnamed: LED15.A, R13.1
unnamed: S8.6, SJ13.2
unnamed: LED2.A, R1.2
unnamed: S8.3, SJ14.2
unnamed: LED3.A, R3.2
unnamed: LED16.A, R17.1
unnamed: LED17.A, R16.2
unnamed: LED18.A, R19.2
unnamed: LED19.A, R20.1
unnamed: LED20.A, R18.1
unnamed: S10.6, SJ17.2
unnamed: S10.3, SJ18.2
unnamed: LED21.A, R22.1
unnamed: LED22.A, R21.2
unnamed: LED23.A, R24.2
unnamed: LED24.A, R25.1
unnamed: LED25.A, R23.1
unnamed: S12.6, SJ21.2
unnamed: S12.3, SJ22.2
unnamed: LED26.A, R27.1
unnamed: LED27.A, R26.2
unnamed: LED28.A, R29.2
unnamed: LED29.A, R30.1
unnamed: LED30.A, R28.1
unnamed: S14.6, SJ25.2
unnamed: S14.3, SJ26.2
unnamed: LED31.A, R32.1
unnamed: LED32.A, R31.2
unnamed: LED4.A, R4.1
unnamed: LED33.A, R34.2
unnamed: LED34.A, R35.1
unnamed: LED35.A, R33.1
unnamed: S16.6, SJ29.2
unnamed: S16.3, SJ30.2
unnamed: LED36.A, R37.1
unnamed: LED37.A, R36.2
unnamed: LED38.A, R39.2
unnamed: LED39.A, R40.1
unnamed: LED40.A, R38.1
unnamed: LED5.A, R2.1
unnamed: S2.6, SJ1.2
unnamed: S2.3, SJ3.2
OUT: JP2.9, JP9.2, LED2.C, S2.2
OUT1: JP15.9, JP17.2, LED7.C, S4.2
OUT2: JP24.9, JP26.2, LED12.C, S6.2
OUT3: JP33.9, JP35.2, LED17.C, S8.2
OUT4: JP42.9, JP44.2, LED22.C, S10.2
OUT5: JP51.9, JP53.2, LED27.C, S12.2
OUT6: JP60.9, JP62.2, LED32.C, S14.2
OUT7: JP69.9, JP71.2, LED37.C, S16.2
PROG: JP1.PROG, JP5.4
PROG1: JP10.PROG, JP12.4
PROG2: JP19.PROG, JP21.4
PROG3: JP28.PROG, JP30.4
PROG4: JP37.PROG, JP39.4
PROG5: JP46.PROG, JP48.4
PROG6: JP55.PROG, JP57.4
PROG7: JP64.PROG, JP66.4
RES: JP2.3, JP9.8
RES1: JP16.4, JP17.14
RES2: JP3.4, JP9.14
RES3: JP15.3, JP17.8
RES4: JP25.4, JP26.14
RES5: JP24.3, JP26.8
RES6: JP34.4, JP35.14
RES7: JP33.3, JP35.8
RES8: JP43.4, JP44.14
RES9: JP42.3, JP44.8
RES10: JP52.4, JP53.14
RES11: JP51.3, JP53.8
RES12: JP61.4, JP62.14
RES13: JP60.3, JP62.8
RES14: JP70.4, JP71.14
RES15: JP69.3, JP71.8
RESET: JP2.6, JP9.5, S3.1
RESET1: JP15.6, JP17.5, S1.1
RESET2: JP24.6, JP26.5, S5.1
RESET3: JP33.6, JP35.5, S7.1
RESET4: JP42.6, JP44.5, S9.1
RESET5: JP51.6, JP53.5, S11.1
RESET6: JP60.6, JP62.5, S13.1
RESET7: JP69.6, JP71.5, S15.1
RSSI: JP2.5, JP9.6, R4.2
RSSI1: JP15.5, JP17.6, R9.2
RSSI2: JP24.5, JP26.6, R15.2
RSSI3: JP33.5, JP35.6, R20.2
RSSI4: JP42.5, JP44.6, R25.2
RSSI5: JP51.5, JP53.6, R30.2
RSSI6: JP60.5, JP62.6, R35.2
RSSI7: JP69.5, JP71.6, R40.2
RTS: JP3.6, JP9.16
RTS1: JP16.6, JP17.16
RTS2: JP25.6, JP26.16
RTS3: JP34.6, JP35.16
RTS4: JP43.6, JP44.16
RTS5: JP52.6, JP53.16
RTS6: JP61.6, JP62.16
RTS7: JP70.6, JP71.16
UART_RX: JP1.0, JP4.2, S2.1
UART_RX1: JP10.0, JP11.2, S4.1
UART_RX2: JP19.0, JP20.2, S6.1
UART_RX3: JP28.0, JP29.2, S8.1
UART_RX4: JP37.0, JP38.2, S10.1
UART_RX5: JP46.0, JP47.2, S12.1
UART_RX6: JP55.0, JP56.2, S14.1
UART_RX7: JP64.0, JP65.2, S16.1
UART_TX: JP1.1, JP4.3, S2.4
UART_TX1: JP10.1, JP11.3, S4.4
UART_TX2: JP19.1, JP20.3, S6.4
UART_TX3: JP28.1, JP29.3, S8.4
UART_TX4: JP37.1, JP38.3, S10.4
UART_TX5: JP46.1, JP47.3, S12.4
UART_TX6: JP55.1, JP56.3, S14.4
UART_TX7: JP64.1, JP65.3, S16.4
VBAT: JP1.VBAT, JP5.1
VBAT1: JP10.VBAT, JP12.1
VBAT2: JP19.VBAT, JP21.1
VBAT3: JP28.VBAT, JP30.1
VBAT4: JP37.VBAT, JP39.1
VBAT5: JP46.VBAT, JP48.1
VBAT6: JP55.VBAT, JP57.1
VBAT7: JP64.VBAT, JP66.1
VIN: JP1.VIN, JP7.1, SJ5.1
VIN1: JP10.VIN, JP14.1, SJ8.1
VIN2: JP19.VIN, JP23.1, SJ12.1
VIN3: JP28.VIN, JP32.1, SJ16.1
VIN4: JP37.VIN, JP41.1, SJ20.1
VIN5: JP46.VIN, JP50.1, SJ24.1
VIN6: JP55.VIN, JP59.1, SJ28.1
VIN7: JP64.VIN, JP68.1, SJ32.1
VUSB: JP1.VUSB, JP7.2
VUSB1: JP10.VUSB, JP14.2
VUSB2: JP19.VUSB, JP23.2
VUSB3: JP28.VUSB, JP32.2
VUSB4: JP37.VUSB, JP41.2
VUSB5: JP46.VUSB, JP50.2
VUSB6: JP55.VUSB, JP59.2
VUSB7: JP64.VUSB, JP68.2
XBEE_VDD: JP2.10, JP9.1, R1.1, R3.1, R11.2, SJ4.2
XBEE_VDD1: JP15.10, JP17.1, R5.1, R6.2, R8.1, SJ7.2
XBEE_VDD2: JP24.10, JP26.1, R10.1, R12.2, R14.1, SJ11.2
XBEE_VDD3: JP33.10, JP35.1, R16.1, R17.2, R19.1, SJ15.2
XBEE_VDD4: JP42.10, JP44.1, R21.1, R22.2, R24.1, SJ19.2
XBEE_VDD5: JP51.10, JP53.1, R26.1, R27.2, R29.1, SJ23.2
XBEE_VDD6: JP60.10, JP62.1, R31.1, R32.2, R34.1, SJ27.2
XBEE_VDD7: JP69.10, JP71.1, R36.1, R37.2, R39.1, SJ31.2

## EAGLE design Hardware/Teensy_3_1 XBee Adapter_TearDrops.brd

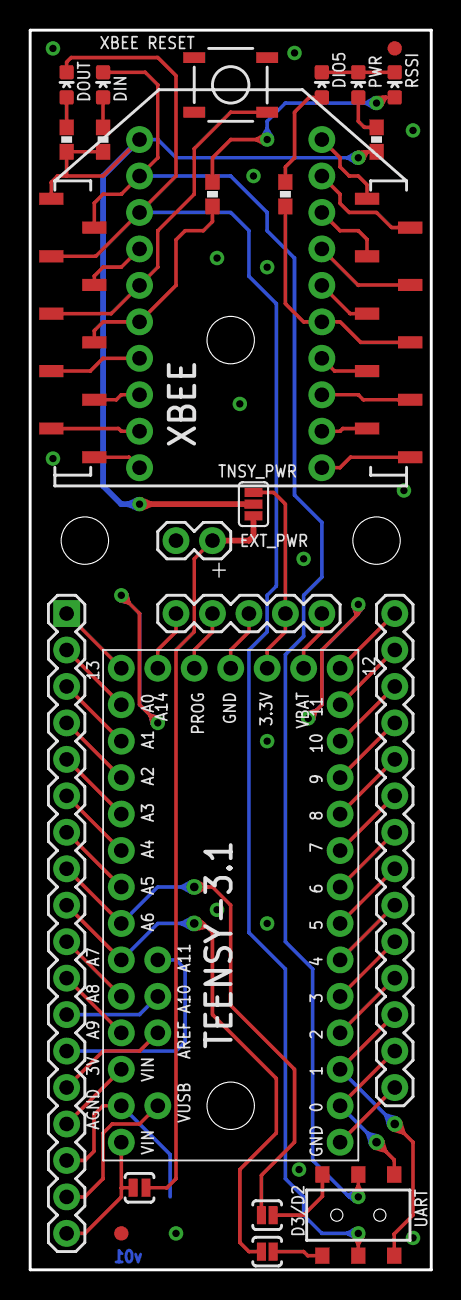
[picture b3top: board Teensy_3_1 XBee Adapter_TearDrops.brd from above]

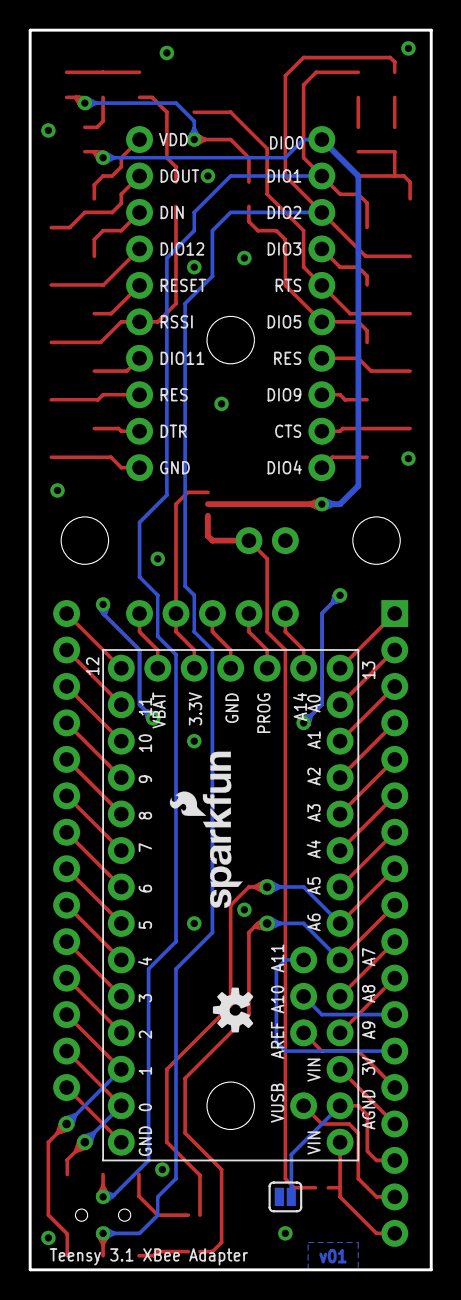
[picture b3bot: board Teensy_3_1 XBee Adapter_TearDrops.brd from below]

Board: 2 copper layers, 27.9 x 86.4 mm, 34 parts (3 on the bottom side), 63 nets.

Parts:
EXT_PWR: M02PTH; 1X02
FID1, FID2: FIDUCIAL1X2; FIDUCIAL-1X2
FRAME1: CREATIVE_COMMONS
JP1: TEENSY-3.1
JP2, JP3: M10NO_SILK_PTH_FEMALE; 1X10_NO_SILK
JP4: M14; 1X14
JP5: 1X05
LED1, LED2: Red; LED-0603
LED3, LED4, LED5: Green; LED-0603
LOGO2: OSHW-LOGOS; OSHW-LOGO-S
LOGO3: SFE_LOGO_NAME_FLAME.1_INCH; SFE_LOGO_NAME_FLAME_.1
R1, R2, R3, R4, R11: 1k; 0603-RES
S2: SWITCH-DPDTSMD; AYZ0202
S3: Reset; TACTILE_SWITCH_SMD
SJ1: D_TX; PAD-JUMPER-2-NC_BY_PASTE_YES_SILK
SJ2: D_TX; SJ_2S
SJ3: D_RX; PAD-JUMPER-2-NC_BY_PASTE_YES_SILK
SJ4: JUMPER-PAD-3-2OF3_NC_BY_PASTE; PAD-JUMPER-3-2OF3_NC_BY_PASTE_YES_SILK_FULL_BOX
SJ5: EXT_JPR; PAD-JUMPER-2-NO_YES_SILK
STANDOFF1, STANDOFF2, STANDOFF3, STANDOFF4: STAND-OFF
U$1: XBEE-1B3; XBEE-SMD
U$2: M18_; 1X18

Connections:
2: JP1.2, JP4.4
3: JP1.3, JP4.5
3.3V: JP1.3.3V, JP5.2, SJ4.3
3V: JP1.3V, U$2.15
4: JP1.4, JP4.6
5: JP1.5, JP4.7
6: JP1.6, JP4.8
7/RX3: JP1.7, JP4.9
8/TX3: JP1.8, JP4.10
9/RX2: JP1.9, JP4.11
10/TX2/CS: JP1.10, JP4.12
11/DOUT: JP1.11, JP4.13
12/DIN: JP1.12, JP4.14
13/SCK: JP1.13, U$2.1
A0/14: JP1.14, U$2.2
A1/15: JP1.15, U$2.3
A2/16: JP1.16, U$2.4
A3/17: JP1.17, U$2.5
A4/18/SDA0: JP1.18, U$2.6
A5/19/SCL0: JP1.19, U$2.7
A6/20: JP1.20, SJ3.1, U$2.8
A7/21: JP1.21, SJ1.1, U$2.9
A8/22: JP1.22, U$2.10
A9/23: JP1.23, U$2.11
A10: JP1.A10, U$2.12
A11: JP1.A11, U$2.13
A14/DAC: JP1.A14/DAC, JP5.5
AGND: JP1.AGND, SJ2.1, U$2.16
AREF: JP1.AREF, U$2.14
CTS: JP3.2, U$1.12
DIO0: JP3.10, U$1.20
DIO1: JP3.9, U$1.19
DIO2: JP3.8, U$1.18
DIO3: JP3.7, U$1.17
DIO4: JP3.1, U$1.11
DIO5: JP3.5, R2.2, U$1.15
DIO9: JP3.3, U$1.13
DIO11: JP2.4, U$1.7
DIO12: JP2.7, U$1.4
DTR: JP2.2, U$1.9
EXT_PWR: EXT_PWR.2, SJ4.1, SJ5.2
GND: EXT_PWR.1, JP1.GND, JP1.GND1, JP2.1, JP4.1, JP5.3, LED1.C, LED4.C, LED5.C, S3.3, SJ2.2, U$1.10
IN: JP2.8, LED3.C, S2.2, U$1.3
unnamed: LED1.A, R11.1
unnamed: LED2.A, R1.2
unnamed: LED3.A, R3.2
unnamed: LED4.A, R4.1
unnamed: LED5.A, R2.1
unnamed: S2.3, SJ1.2
unnamed: S2.6, SJ3.2
OUT: JP2.9, LED2.C, S2.5, U$1.2
PROG: JP1.PROG, JP5.4
RES: JP2.3, U$1.8
RES2: JP3.4, U$1.14
RESET: JP2.6, S3.1, U$1.5
RSSI: JP2.5, R4.2, U$1.6
RTS: JP3.6, U$1.16
UART_RX: JP1.0, JP4.2, S2.4
UART_TX: JP1.1, JP4.3, S2.1
VBAT: JP1.VBAT, JP5.1
VIN: JP1.VIN, SJ5.1, U$2.18
VUSB: JP1.VUSB, U$2.17
XBEE_VDD: JP2.10, R1.1, R3.1, R11.2, SJ4.2, U$1.1

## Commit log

2015-02-20 Initial Hardware Commit.
2015-02-20 Fixed vector font
2015-02-24 Opened the board up a bit
2015-02-24 Removed teardrops example
2015-02-26 Fixed silk. Preparing for first proto
2015-02-26 Fliping bottom silk labels
2015-02-27 Completed first round of QC notes
2015-03-02 Fixed airwire, updated revision
2015-03-19 SW examples for UART1 and SUART added
2015-03-20 Prototype tested and documented. Silkscreen was adjusted and two 0603 components were twisted so that they are in the same direction as the others.
2015-03-30 Final proto fixes
2015-03-31 Serviced github issues and deployed gitignore file
2015-03-31 Removed excessive s#n files
2015-04-02 Fixed A-B button swap
2015-04-15 removed micro fids, added regular 1x2
2015-04-15 created panel v10
2015-05-14 Fixed sketches
2015-05-14 Changed directory structure
2015-06-05 Fixing documentation
2015-06-17 Repo housekeeping and example code comment proofread
2015-06-19 updating README, file structure for release
2015-06-19 Adding license file
2020-06-01 Remove depreciated definitions and update functions
    It appears that the behavior of a function has been removed and `BYTE` is no longer a keyword in Arduino after a certain version => https://forum.arduino.cc/index.php?topic=85382.msg639273#msg639273 .
    Minor update so that the users can still send/receive characters.

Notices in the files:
parts and their libraries:
SparkFun-Connectors: Licensing: Creative Commons ShareAlike 4.0 International - https://creativecommons.org/licenses/by-sa/4.0
SparkFun-Aesthetics: Released under the Creative Commons Attribution Share-Alike 4.0 License
SparkFun-Aesthetics: Released under the Creative Commons
